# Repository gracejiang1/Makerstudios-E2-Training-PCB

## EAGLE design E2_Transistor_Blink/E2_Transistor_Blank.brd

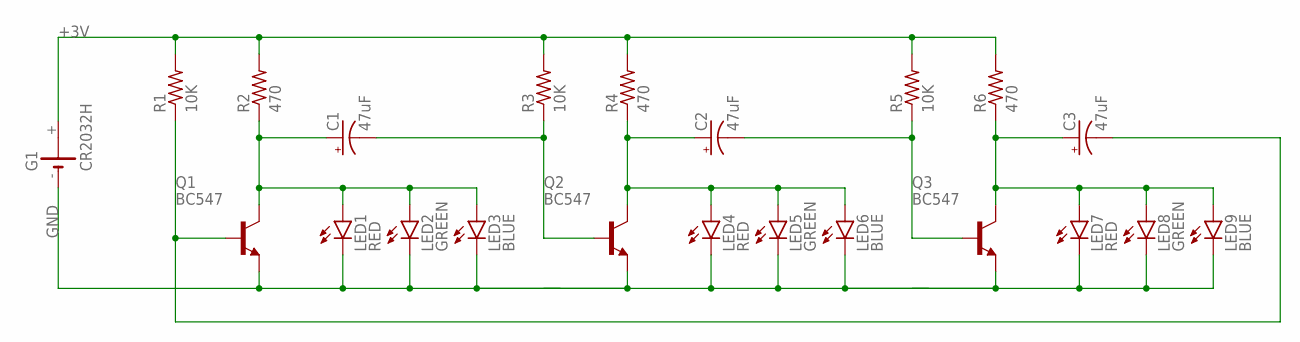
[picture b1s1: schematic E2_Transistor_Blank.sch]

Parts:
C1, C2, C3: 47uF; E1,8-4
G1: CR2032H
LED1, LED4, LED7: RED; LED5MM
LED2, LED5, LED8: GREEN; LED5MM
LED3, LED6, LED9: BLUE; LED5MM
Q1, Q2, Q3: BC547; TO92
R1, R3, R5: 10K; 0309/12
R2, R4, R6: 470; 0309/12

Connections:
+3V: G1.+, R1.2, R2.2, R3.2, R4.2, R5.2, R6.2
GND: G1.-, LED1.K (C), LED2.K (C), LED3.K (C), LED4.K (C), LED5.K (C), LED6.K (C), LED7.K (C), LED8.K (C), LED9.K (C), Q1.1 (E), Q2.1 (E), Q3.1 (E)
unnamed: C1.+, LED1.A, LED2.A, LED3.A, Q1.3 (C), R2.1
unnamed: C1.-, Q2.2 (B), R3.1
unnamed: C2.+, LED4.A, LED5.A, LED6.A, Q2.3 (C), R4.1
unnamed: C3.+, LED7.A, LED8.A, LED9.A, Q3.3 (C), R6.1
unnamed: C3.-, Q1.2 (B), R1.1
unnamed: C2.-, Q3.2 (B), R5.1

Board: 2 copper layers, 22 parts (0 on the bottom side), 8 nets, no tracks yet.

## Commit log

2019-10-31 add E2 LED Chaser Transistor Circuit
